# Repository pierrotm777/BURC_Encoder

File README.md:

# BURC_Encoder
 Universal RC Box System.  
 
 The BURC modules use the RCUL protocol by Rc-Navy.

## Rc-Navy
The BURC system is build by Philippe Loussouarn ([Rc-Navy](http://p.loussouarn.free.fr/index.html)). 

## Presentation of the BURC system
[What's BURC](https://p-loussouarn-free-fr.translate.goog/arduino/exemple/RCUL/RCUL.html?_x_tr_sch=http&_x_tr_sl=auto&_x_tr_tl=en&_x_tr_hl=en)

## Compatibles modules usable with BURC
All these modules behind
- [Ms8 v2](https://github.com/Ingwie/OpenAVRc_Hw/tree/V3/MutltiSwitch_Sw8_V2)  
- [Ms16](https://github.com/Ingwie/OpenAVRc_Hw/tree/V3/MultiSwitch_Sw16-ProMicro)  
- [Sound&SmokeModule](https://github.com/Ingwie/OpenAVRc_Hw/tree/V3/Sound%26SmokeModule)  
- [Xany2Msx](https://github.com/Ingwie/OpenAVRc_Hw/tree/V3/Xany2Msx/Firmware_Msx)  
- [Xany2Misc](https://github.com/Ingwie/OpenAVRc_Hw/tree/V3/Xany2Msx/Firmware_Misc)  
- Hall sensor:  
  * [Hall I2C sensor](https://github.com/Ingwie/OpenAVRc_Hw/tree/V3/Capteur_Hall_I2C)  
  * [Hall I2C sensor mini](https://github.com/Ingwie/OpenAVRc_Hw/tree/V3/Capteur_Hall_I2C_Mini)  
- [MultiSwitch_MosFet](https://github.com/Ingwie/OpenAVRc_Hw/tree/V3/MultiSwitch_MosFet)  
- [Ms8 Pulseq](https://github.com/Ingwie/OpenAVRc_Hw/tree/V3/PulseSeq) 
- [Servo 360°]() 

## Build BURC
### Schematic  
Encoder:  
  
16 switchs by I2C bus:  
  
16 switchs on Arduino:  

### Boards  
Two cards make up the BURC system.
The BURC Encoder is connected to the transmitter over a **CPPM** input or a **SBUS** input.
- The BURC Encoder:
  * Encoder board (include 8 switchs, 1 360° hall sensor and 1 slider, need one proportional channel) 
  Can command up to 128 fonctions (8x16) by exemple 8 Ms16 modules, use 1 channel for each 16 switchs module.  

  <table border="2">
  <tr>
  <td></td>
  <td></td>
  </tr>
  </table>
  
  The hall sensor command a Schottel motor type by rotation, and the slider command the motor's power.  
  This board is the **main board** system and can command **several 16 switchs** board.  
  The interface between all the boards use an **I2C** bus.  

  The same board can be used for the left or right motor, and assume to wire only one of the two hall sensor an the 8 first switchs.  
  The second board will command the 8 other switchs and the second slider (No need another arduino Pro Mini in the second circuit board) .  
  An Attiny85 receive these orders from the first board and command the second hall sensor and the second slider.  
  A dashboard exemple for two motors:  
  <table border="2">
  <tr>
  <td></td>
  </tr>
  </table>
    
  * Encoder symplified board (include 16 switchs or 8 switchs and 6 potentiometers, need one proportional channel) 
  Can command up to 128 fonctions (8x16) by exemple 8 Ms16 modules, use 1 channel for each 16 switchs module.  

  <table border="2">
  <tr>
  <td></td>
  </tr>
  </table>
  
  You need to remove the resistor's LED on pin D13 (C10 signal).  

- The Switch board:

  16 Switchs board (need one proportional channel) 
  Each switch can command 1 fonction.  
  The type of command depend of the [Ms8](https://github.com/Ingwie/OpenAVRc_Hw/blob/V3/MutltiSwitch_Sw8_V2/MS8-Xany-V2_Manuel_Utilisateur.pdf)/[Ms16](https://github.com/Ingwie/OpenAVRc_Hw/blob/V3/MultiSwitch_Sw16-ProMicro/MS16-Xany_Manuel_Utilisateur.pdf) possibilities.    
  This board read 16 switchs by 1 MCP23017 or 2 PCF8574 or 1 PCF8575.
  <table border="2">
  <tr>
  <td></td>
  <td></td>
  </tr>
  </table>  
  
  A main board coupled to  a second board and 2 16 switchs boards:
  <table border="2">
  <tr>
  <td></td>
  </tr>
  </table>  
  
  A main board and a 48 switchs coupled:
  <table border="2">
  <tr>
  <td></td>
  </tr>
  </table>  

### Firmware upload for Pro Mini
- Windows:  
The best method is to use [Xloader](https://github.com/pierrotm777/BURC_Encoder/blob/main/PROG/Windows/XLoader.zip).  
The last firmware is the version [v0.14](https://github.com/pierrotm777/BURC_Encoder/blob/main/PROG/Windows/BURC_CODER_V0_14.hex).  

- Other Os:
Use you Arduino IDE for find witch command to use.
In my case, the command is :  
  
  * replace the hex file path C:\Users\pierrot\AppData\Local\Temp\arduino_build_879913/Blink.ino.hex by your firmware path.  
  * create a script file with this change.  

### Firmware upload for Attiny85
  * use an USBAsp programmer and [ARDUDESS Gui](https://github.com/ZakKemble/AVRDUDESS/releases/) or an [Arduino Uno board](https://www.instructables.com/Programming-ATtinys-Micro-Controllers-With-Arduino)
  * define the fuses (for 16Mhz internal mode), low=0xF1, high=0xDF, extended=0xFF
  * last firmware is the version [v2.2](https://github.com/pierrotm777/BURC_Encoder/blob/main/PROG/Windows/HallAna2A1335_V2_2.hex).  

### Exemple BURC build
- You will find [here](https://cults3d.com/fr/mod%C3%A8le-3d/jeu/burc-pad) an exemple of 3d files by **croky_b** witch accept all the BURC's boards.  

## Configure the BURC Encoder
  * Pro Mini:
    * Connect a FTDI interface to the Arduino Pro Mini and your PC.
    * Use a terminal for send your commands.
    * Set your terminal with 115200 bauds, 8 bits, no parity, 1 bit stop and CR or CRLF (see LIGNE.TERM).
    * Type ENTER key for see the module's version.

  * Attiny85 (360° encoder) A push button allows:
    * calibrating the analog sensor (min and max): before powering the ATtiny85, press the Push button and hold it for  1 - 2 seconds.
    * setting the I2C address: before powering the ATtiny85, press the Push button and hold it for more than 4 seconds.  
      Additionally, it can read an analogic input (0/5V)

## Settings usables
The list of messages that can be transported in each RCUL instance is:  
- SW1-SW8:   the state of 8 contacts of the 8 contacts of an 8 I/O I/O extender or a 16 I/O extender or the first 8 contacts of the 16 native contacts of the Arduino
- SW9-SW16:  the state of the last 8 contacts of a 16 I/O extender or the last 8 contacts of the 16 native contacts of the Arduino
- SW1-SW16:  the state of 16 contacts of a 16 I/O extender or of the 16 native contacts of the Arduino
- ANGLE:     the value of the angle of a 360° angle sensor
- ANGLE+ANA: the value of the angle of a 360° angular sensor + an analog value  

On the encoder there are 16 native contacts from C1 to C16.  
Among C8 to C16, 6 are also analog inputs which correspond to pins C11 to C16.  
So C11 to C16 are also ANA1 to ANA6 (these are my names, not the names of the "arduino" pins):  
We therefore have 6 analog channels at our disposal (just as we wire a pot there instead of an switch or push button).  

We can make extended RCUL messages of the type:  
**RCUL1.MESSAGE=C1-C8@0x00+ANA1** (which will transmit 8 contact states + an 8-bit ana value:  
You obviously have to wire a knob to pin C11).  
**RCUL2.MESSAGE=C9-C16@0x24+ANA2** (which will transmit 16 contact states + an 8-bit ana value:  
You obviously have to wire a knob to pin C12).  

So, with **RCUL1.MESSAGE=C1-C8@0x00+ANA1** or **RCUL2.MESSAGE=C9-C16@0x24+ANA2**,  
for an MS8 (V1 or V2), you can control the 8 outputs + the additional proportional output.  
You can also order the Sound&Smoke module which uses the 8 contacts to launch 8  
different sounds and the ana value to adjust the volume of the DF Player from the transmitter.  

We can also do:
**RCUL3.MESSAGE=C1-C16@0x25+ANA3** (which will transmit 16 contact states + an 8-bit analog value:  
You obviously have to wire a knob to pin C12)
So, with **RCUL3.MESSAGE=C1-C16@0x25+ANA3** for an MS16, you can control the 16 outputs + the additional proportional output.  

So, if we want to use the first 8 contacts C1 to C8 of your 16-input I2C extender at address 0x24,  
we just have to create another RCUL instance in which we refer to the first 8 contacts: **RCUL5.MESSAGE=C1-C8@0x24**
And with RCUL5 we can, for example, order another MS8.
So we will have the first 8 contacts of the I2C extender with 16 inputs (at address 0x24) used by RCUL5 to control an MS8 (for example) 
and the last 8 contacts of the 16-input I2C extender (at address 0x24) used by RCUL2 (which also uses ANA2) to control a Sound&Smoke.

It is possible to directly map an analog value (ANA1 to AN6), inverted or not, to a channel.  
To do this, you must use the command **RCULx.MESSAGE=RC.ANA[_INV]y** with x=RCUL instance number and y is the ANA channel number (from 1 to 6):  
Example: **RCUL4.MESSAGE=RC.ANA_INV1**  
A simple solution for build a little 6 channels hanset WITH BURC features.  

Debug method:  
To test an RCUL channel in CPPM, we loop pin8 back to pin9 and we do an **RX.MODE=RCUL4@CPPM4** and after an **RX.DBG=1** command.  

## I2C Devices address
<pre>
PCF8574         <b>0x20 to 0x23</b>  
MCP23017        <b>0x24 to 0x27</b>  
PCF8574A        <b>0x38 to 0x3B</b> (very difficult to find)  
PCF8575         <b>0x24 to 0x27</b>  
PCF8575A        <b>0x3C to 0x3F</b> (very difficult to find)  
ANGLE SENSOR    <b>0x0C to 0x0F</b>  
</pre>

Exemple of configuration:
```
CONF?
LANG=FR
LIGNE.TERM=CRLF
ECOLAGE.MODE=CPPM_OUT
CPPM.MODU=NEG
CPPM.ENTETE=300
CPPM.VOIE.NB=8
CPPM.PERIODE=22500
RCUL.REPET=2
RCUL1.VOIE=5
RCUL1.MESSAGE=ANGLE+ANA@0x0C
RCUL1.TEST=OFF
RCUL2.VOIE=6
RCUL2.MESSAGE=C9-C16@0x24
RCUL2.TEST=OFF
RCUL3.VOIE=8
RCUL3.MESSAGE=C1-C8@0x24+ANA1
RCUL3.TEST=OFF
RCUL4.VOIE=7
RCUL4.MESSAGE=RC.ANA_INV1
RCUL4.TEST=OFF
RCUL5.VOIE=OFF
RCUL5.MESSAGE=C1-C8@0x00
RCUL5.TEST=OFF
RCUL6.VOIE=OFF
RCUL6.MESSAGE=C1-C8@0x00
RCUL6.TEST=OFF
RX.MODE=RCUL6@CPPM6
RX.DBG=0
```

<pre>
- LANG=FR                       define language (FR or UK)  
- LIGNE.TERM=CRLF               define terminal return (CR or CRLF)  
- ECOLAGE.MODE=CPPM_OUT         CPPM_OUT+CPPM_IN/CPPM_OUT/SBUS_OUT;FUTABA[_INV] Defines the transmitter training mode
- CPPM.MODU=NEG                 CPPM signal is build with negative pulses (POS is possible)  
- CPPM.ENTETE=300               300 first width CPPM pulse  
- CPPM.VOIE.NB=8                CPPM build 8 channels  
- CPPM.PERIODE=22500            CPPM periode in mS
- SBUS.SPEED=NORMAL				NORMAL/FAST Defines the SBUS speed (NORMAL=14ms, FAST=7ms)  
- RCUL.REPET=2                  the encoder repeats the same thing twice for a better transmission result  
- RCUL1.MESSAGE=ANGLE+ANA@0x0C  for command an azimutal motor (direction and motor)  
- RCUL2.MESSAGE=C9-C16@0x24     8 buttons on MCP23017 (address 0x24)  
- RCUL3.MESSAGE=C1-C8@0x24+ANA1 8 buttons on MCP23017 and analog button (module Sound&Smoke for 8 sounds et volume)
- RCUL4.MESSAGE=RC.ANA_INV2     1 analogique channel inverted  
</pre>

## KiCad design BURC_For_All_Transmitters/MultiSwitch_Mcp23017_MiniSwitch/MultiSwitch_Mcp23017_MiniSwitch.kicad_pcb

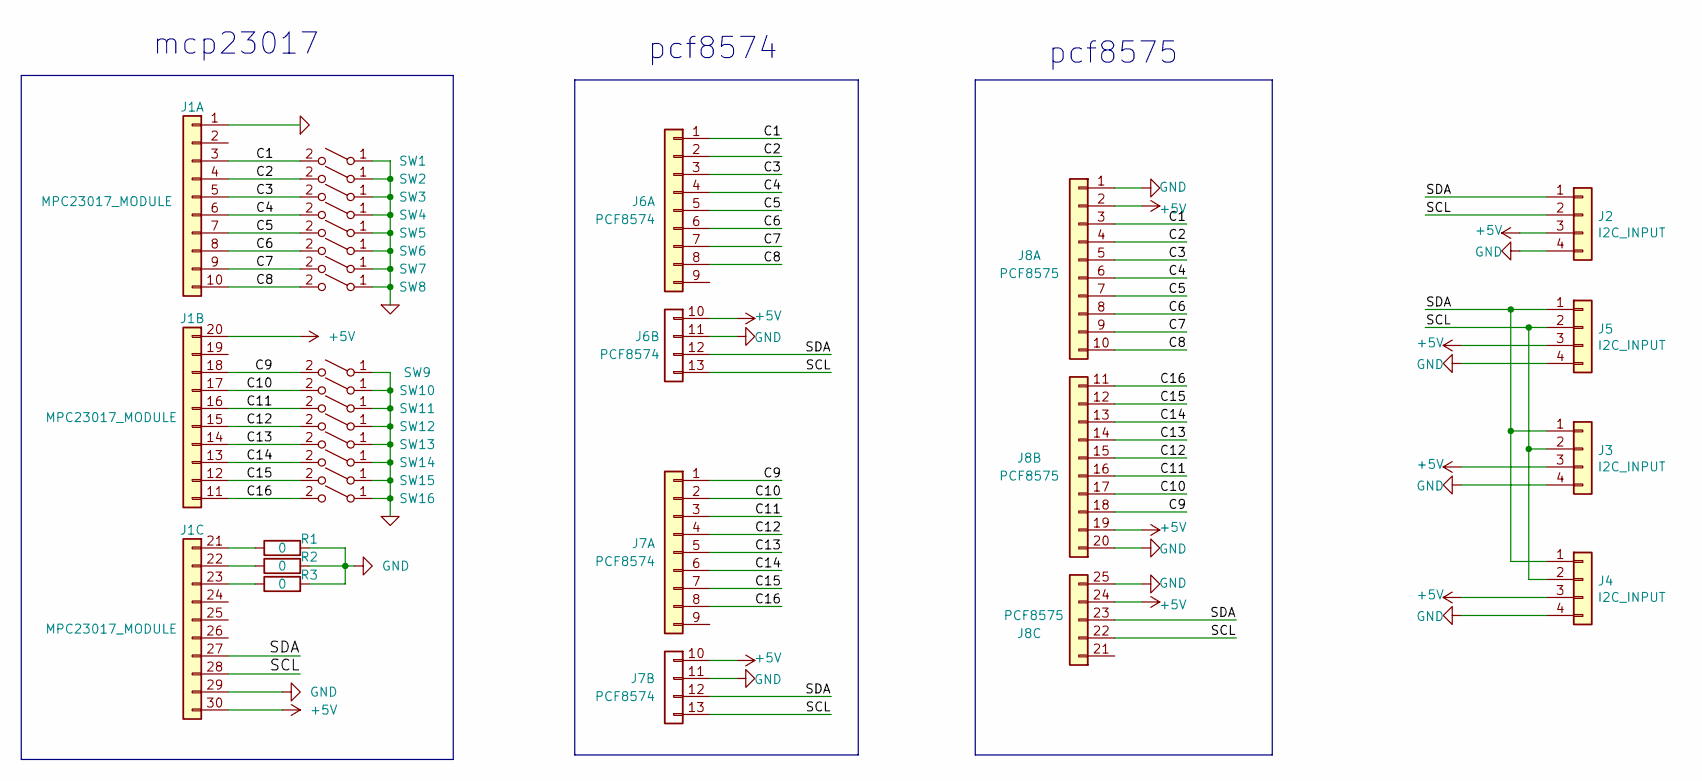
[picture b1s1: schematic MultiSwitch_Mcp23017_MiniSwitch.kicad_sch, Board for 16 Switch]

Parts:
J1: MPC23017_MODULE; MCP23017_MODULE
J2, J4: I2C_INPUT; PinHeader_1x04_P2.54mm_Horizontal
J3, J5: I2C_INPUT; PinSocket_1x04_P2.54mm_Horizontal
J6, J7: PCF8574; PCF8574_BreakOut
J8: PCF8575; PCF8575_Breakout_Dbl
R1, R2, R3: 0; R_0805_2012Metric_Pad1.20x1.40mm_HandSolder
SW1, SW2, SW3, SW4, SW5, SW6, SW7, SW8, SW9, SW10, SW11, SW12, SW13, SW14, SW15, SW16: SW_SPST; Interrupteur_SPDT_2Pins

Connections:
+5V: J1.20, J1.30, J2.3, J3.3, J4.3, J5.3, J6.10 (Pin_4), J7.10 (Pin_4), J8.2, J8.19, J8.24
/C1: J1.3, J6.1, J8.3, SW1.2 (B)
/C2: J1.4, J6.2, J8.4, SW2.2 (B)
/C3: J1.5, J6.3, J8.5, SW3.2 (B)
/C4: J1.6, J6.4, J8.6, SW4.2 (B)
/C5: J1.7, J6.5, J8.7, SW5.2 (B)
/C6: J1.8, J6.6, J8.8, SW6.2 (B)
/C7: J1.9, J6.7, J8.9, SW7.2 (B)
/C8: J1.10, J6.8, J8.10, SW8.2 (B)
/C9: J1.18, J7.1, J8.18, SW9.2 (B)
/C10: J1.17, J7.2, J8.17, SW10.2 (B)
/C11: J1.16, J7.3, J8.16, SW11.2 (B)
/C12: J1.15, J7.4, J8.15, SW12.2 (B)
/C13: J1.14, J7.5, J8.14, SW13.2 (B)
/C14: J1.13, J7.6, J8.13, SW14.2 (B)
/C15: J1.12, J7.7, J8.12, SW15.2 (B)
/C16: J1.11, J7.8, J8.11, SW16.2 (B)
/SCL: J1.28, J2.2, J3.2, J4.2, J5.2, J6.13 (Pin_1), J7.13 (Pin_1), J8.22
/SDA: J1.27, J2.1, J3.1, J4.1, J5.1, J6.12 (Pin_2), J7.12 (Pin_2), J8.23
GND: J1.1, J1.29, J2.4, J3.4, J4.4, J5.4, J6.11 (Pin_3), J7.11 (Pin_3), J8.1, J8.20, J8.25, R1.2, R2.2, R3.2, SW1.1 (A), SW2.1 (A), SW3.1 (A), SW4.1 (A), SW5.1 (A), SW6.1 (A), SW7.1 (A), SW8.1 (A), SW9.1 (A), SW10.1 (A), SW11.1 (A), SW12.1 (A), SW13.1 (A), SW14.1 (A), SW15.1 (A), SW16.1 (A)
unnamed: J1.21, R1.1
unnamed: J1.22, R2.1
unnamed: J1.23, R3.1

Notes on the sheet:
pcf8575
pcf8574
mcp23017

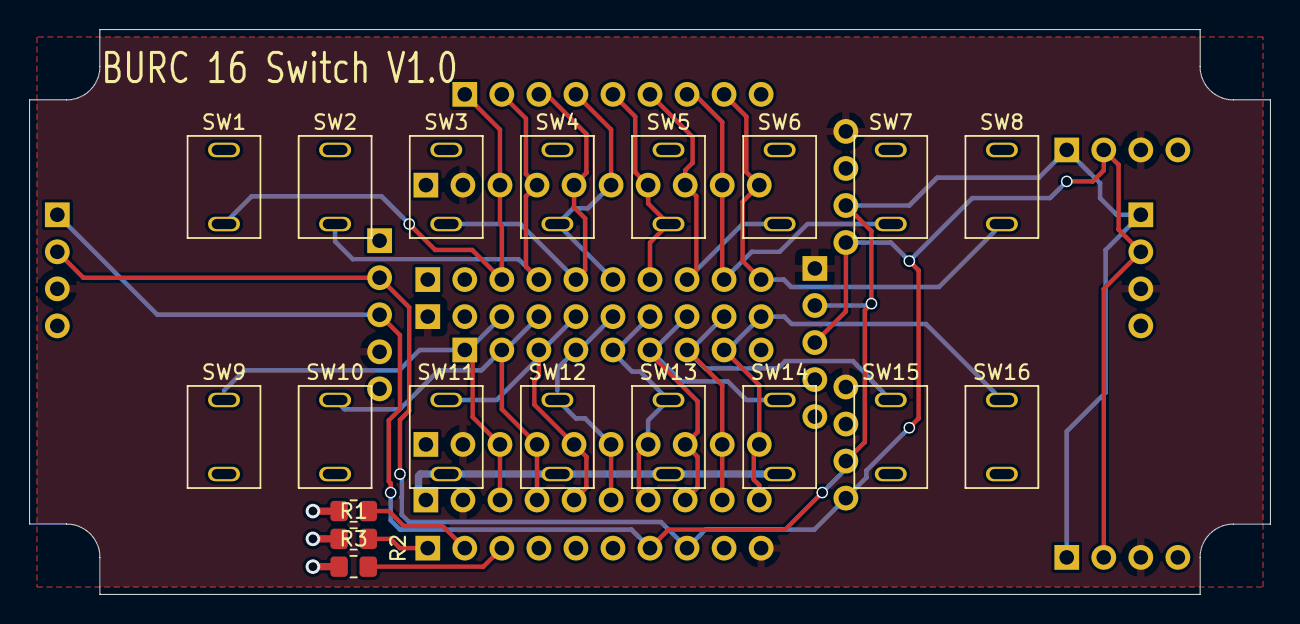
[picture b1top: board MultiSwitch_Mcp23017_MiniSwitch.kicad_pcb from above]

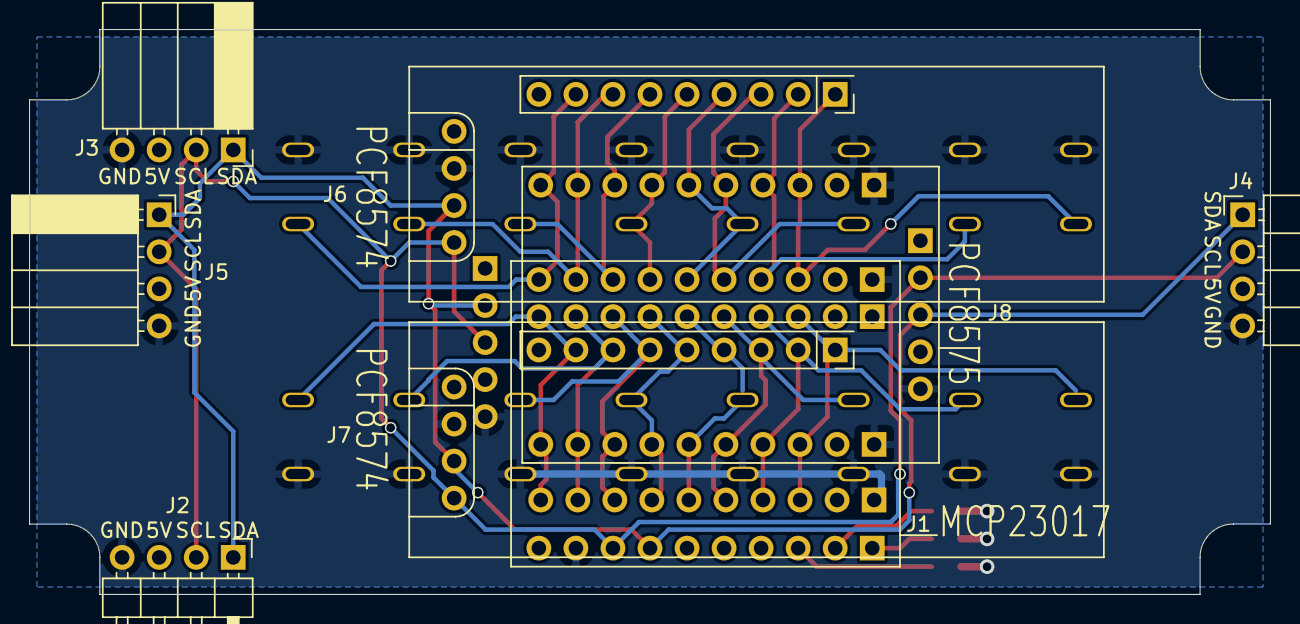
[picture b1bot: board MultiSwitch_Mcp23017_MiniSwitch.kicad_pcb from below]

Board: 2 copper layers, 85.1 x 38.7 mm, 27 parts (8 on the bottom side), 23 nets.

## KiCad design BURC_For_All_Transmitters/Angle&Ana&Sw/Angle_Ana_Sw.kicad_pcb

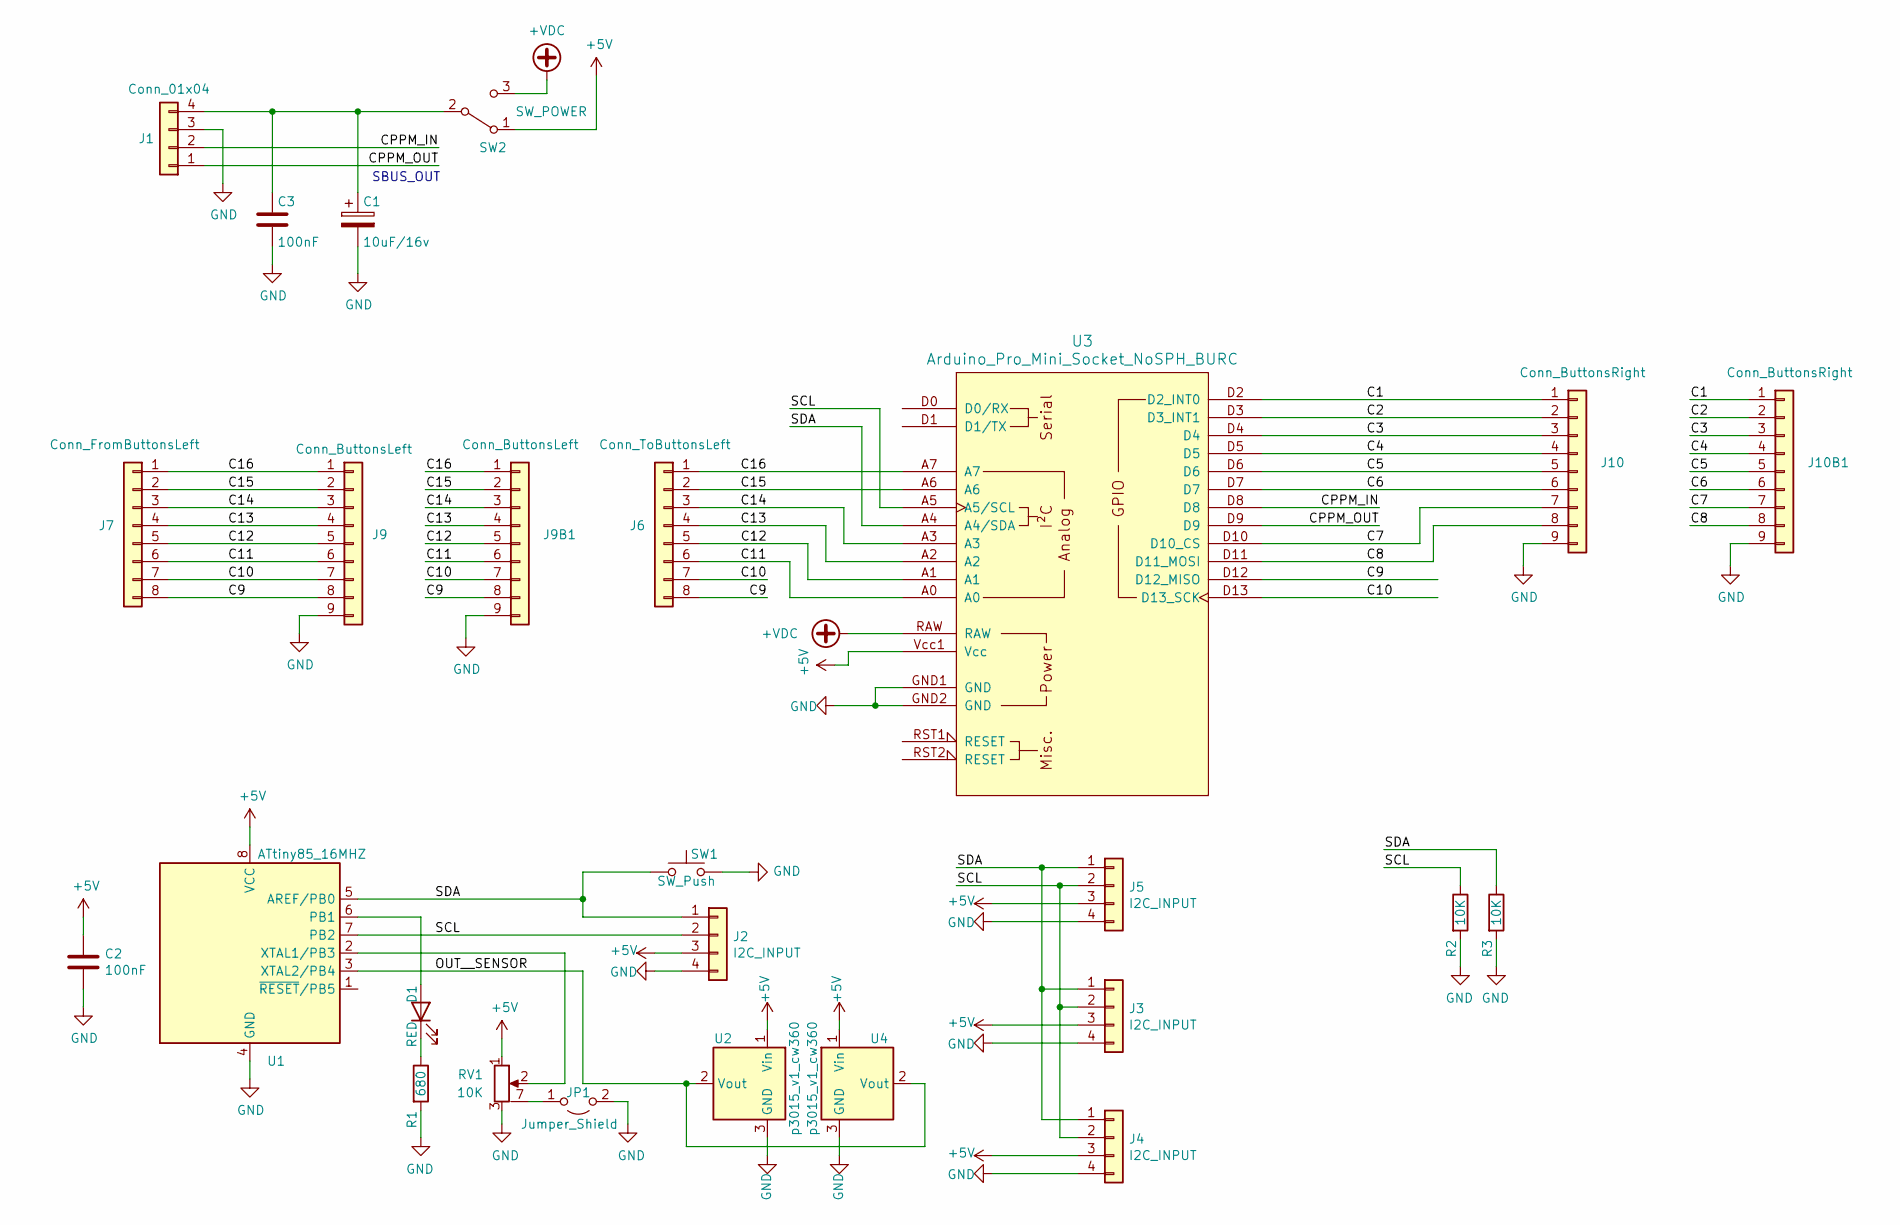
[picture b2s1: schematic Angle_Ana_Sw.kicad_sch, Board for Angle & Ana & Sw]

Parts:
C1: 10uF/16v; C_Radial_D8.0mm_H7.0mm_P3.50mm
C2, C3: 100nF; C_Rect_L7.0mm_W3.5mm_P5.00mm
D1: RED; LED_D3.0mm_Horizontal_O1.27mm_Z2.0mm
J1: Conn_01x04; PinHeader_1x04_P2.54mm_Horizontal
J2, J4: I2C_INPUT; PinHeader_1x04_P2.54mm_Horizontal
J3, J5: I2C_INPUT; PinSocket_1x04_P2.54mm_Horizontal
J6: Conn_ToButtonsLeft; PinSocket_2x04_P2.54mm_Horizontal
J7: Conn_FromButtonsLeft; PinHeader_2x04_P2.54mm_Horizontal
J9: Conn_ButtonsLeft; JST_PH_B9B-PH-K_1x09_P2.00mm_Vertical
J9B1: Conn_ButtonsLeft; PinHeader_1x09_P2.54mm_Vertical
J10: Conn_ButtonsRight; JST_PH_B9B-PH-K_1x09_P2.00mm_Vertical
J10B1: Conn_ButtonsRight; PinHeader_1x09_P2.54mm_Vertical
JP1: Jumper_Shield; SolderJumper-2_P1.3mm_Open_Pad1.0x1.5mm
R1: 680; R_Axial_DIN0204_L3.6mm_D1.6mm_P5.08mm_Horizontal
R2, R3: 10K; R_Axial_DIN0204_L3.6mm_D1.6mm_P5.08mm_Horizontal
RV1: 10K; PTA2043-2015CPB103
SW1: SW_Push; SW_PUSH_ANGLED
SW2: SW_POWER; PinHeader_1x03_P2.54mm_Vertical
U1: ATtiny85_16MHZ; DIP-8_W7.62mm
U2, U4: p3015_v1_cw360
U3: Arduino_Pro_Mini_Socket_NoSPH_BURC

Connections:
+5V: C2.1, J2.3, J3.3, J4.3, J5.3, RV1.1, SW2.1 (A), U1.8 (VCC), U2.1 (Vin), U3.Vcc1 (Vcc), U4.1 (Vin)
+VDC: SW2.3 (C), U3.RAW
/C1: J10.1, J10B1.1, U3.D2 (D2_INT0)
/C2: J10.2, J10B1.2, U3.D3 (D3_INT1)
/C3: J10.3, J10B1.3, U3.D4
/C4: J10.4, J10B1.4, U3.D5
/C5: J10.5, J10B1.5, U3.D6
/C6: J10.6, J10B1.6, U3.D7
/C7: J10.7, J10B1.7, U3.D10 (D10_CS)
/C8: J10.8, J10B1.8, U3.D11 (D11_MOSI)
/C9: J6.8, J7.8, J9.8, J9B1.8, U3.D12 (D12_MISO)
/C10: J6.7, J7.7, J9.7, J9B1.7, U3.D13 (D13_SCK)
/C11: J6.6, J7.6, J9.6, J9B1.6, U3.A0
/C12: J6.5, J7.5, J9.5, J9B1.5, U3.A1
/C13: J6.4, J7.4, J9.4, J9B1.4, U3.A2
/C14: J6.3, J7.3, J9.3, J9B1.3, U3.A3
/C15: J6.2, J7.2, J9.2, J9B1.2, U3.A6
/C16: J6.1, J7.1, J9.1, J9B1.1, U3.A7
/CPPM_IN: J1.2, U3.D8
/CPPM_OUT: J1.1, U3.D9
/OUT__SENSOR: U1.3 (XTAL2/PB4), U2.2 (Vout), U4.2 (Vout)
/SCL: J2.2, J3.2, J4.2, J5.2, R2.1, U1.7 (PB2), U3.A5 (A5/SCL)
/SDA: J2.1, J3.1, J4.1, J5.1, R3.1, SW1.1, U1.5 (AREF/PB0), U3.A4 (A4/SDA)
GND: C1.2, C2.2, C3.2, J1.3, J2.4, J3.4, J4.4, J5.4, J9.9, J9B1.9, J10.9, J10B1.9, JP1.2 (B), R1.2, R2.2, R3.2, RV1.3, SW1.2, U1.4 (GND), U2.3 (GND), U3.GND1 (GND), U3.GND2 (GND), U4.3 (GND)
unnamed: D1.2 (A), U1.6 (PB1)
unnamed: D1.1 (K), R1.1
unnamed: C1.1, C3.1, J1.4, SW2.2 (B)
unnamed: JP1.1 (A), RV1.7 (Shield)
unnamed: RV1.2, U1.2 (XTAL1/PB3)

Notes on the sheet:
SBUS_OUT

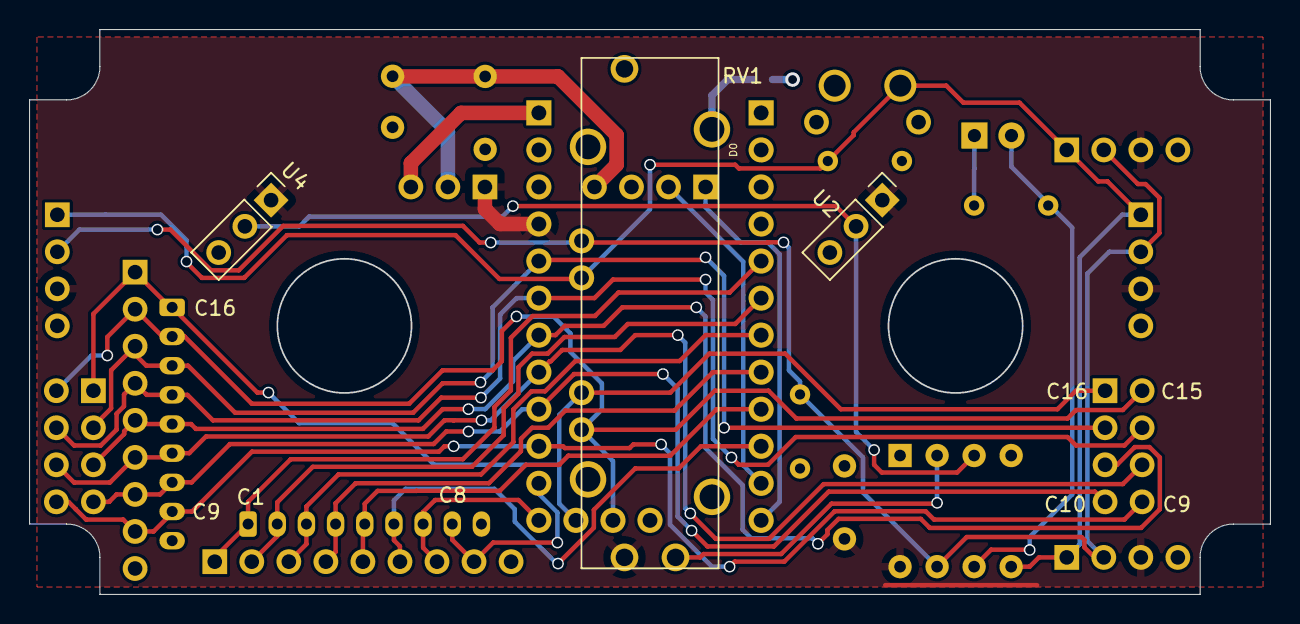
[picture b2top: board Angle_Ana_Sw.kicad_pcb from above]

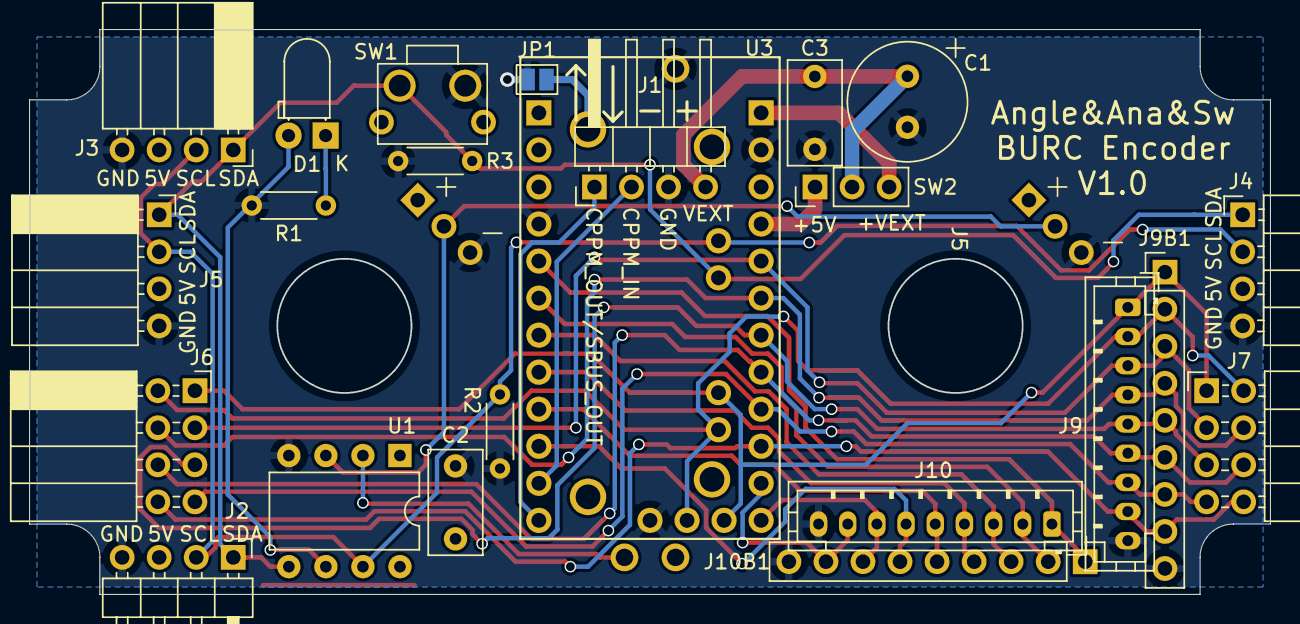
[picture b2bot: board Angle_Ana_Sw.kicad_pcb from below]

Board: 2 copper layers, 85.0 x 38.7 mm, 26 parts (23 on the bottom side), 29 nets.

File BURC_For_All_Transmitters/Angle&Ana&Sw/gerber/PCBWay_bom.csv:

designator,quantity,value,pack,mpn,mount_type
C1,1,10uF/16v,C_Radial_D8.0mm_H7.0mm_P3.50mm,,tht
"C2, C3",2,100nF,C_Rect_L7.0mm_W3.5mm_P5.00mm,,tht
D1,1,RED,LED_D3.0mm_Horizontal_O1.27mm_Z2.0mm,,tht
J1,1,Conn_01x04,PinHeader_1x04_P2.54mm_Horizontal,,tht
"J10, J9",2,Conn_ButtonsLeft,JST_PH_B9B-PH-K_1x09_P2.00mm_Vertical,,tht
"J2, J4",2,I2C_INPUT,PinHeader_1x04_P2.54mm_Horizontal,,tht
"J3, J5",2,I2C_INPUT,PinSocket_1x04_P2.54mm_Horizontal,,tht
J6,1,Conn_ToButtonsRight,PinSocket_2x04_P2.54mm_Horizontal,,tht
J7,1,Conn_FromButtonsLeft,PinHeader_2x04_P2.54mm_Horizontal,,tht
R1,1,680,R_Axial_DIN0204_L3.6mm_D1.6mm_P5.08mm_Horizontal,,tht
RV1,1,10K,PTA2043-2015CPB103,,tht
SW1,1,SW_Push,SW_PUSH_ANGLED,,tht
SW2,1,SW_POWER,PinHeader_1x03_P2.54mm_Vertical,,tht
U1,1,ATtiny85,DIP-8_W7.62mm,,tht
"U2, U4",2,p3015_v1_cw360,p3015_v1_cw360,,tht
U3,1,Arduino_Pro_Mini,Arduino_Pro_Mini_Socket_NoSPH_BURC,,tht

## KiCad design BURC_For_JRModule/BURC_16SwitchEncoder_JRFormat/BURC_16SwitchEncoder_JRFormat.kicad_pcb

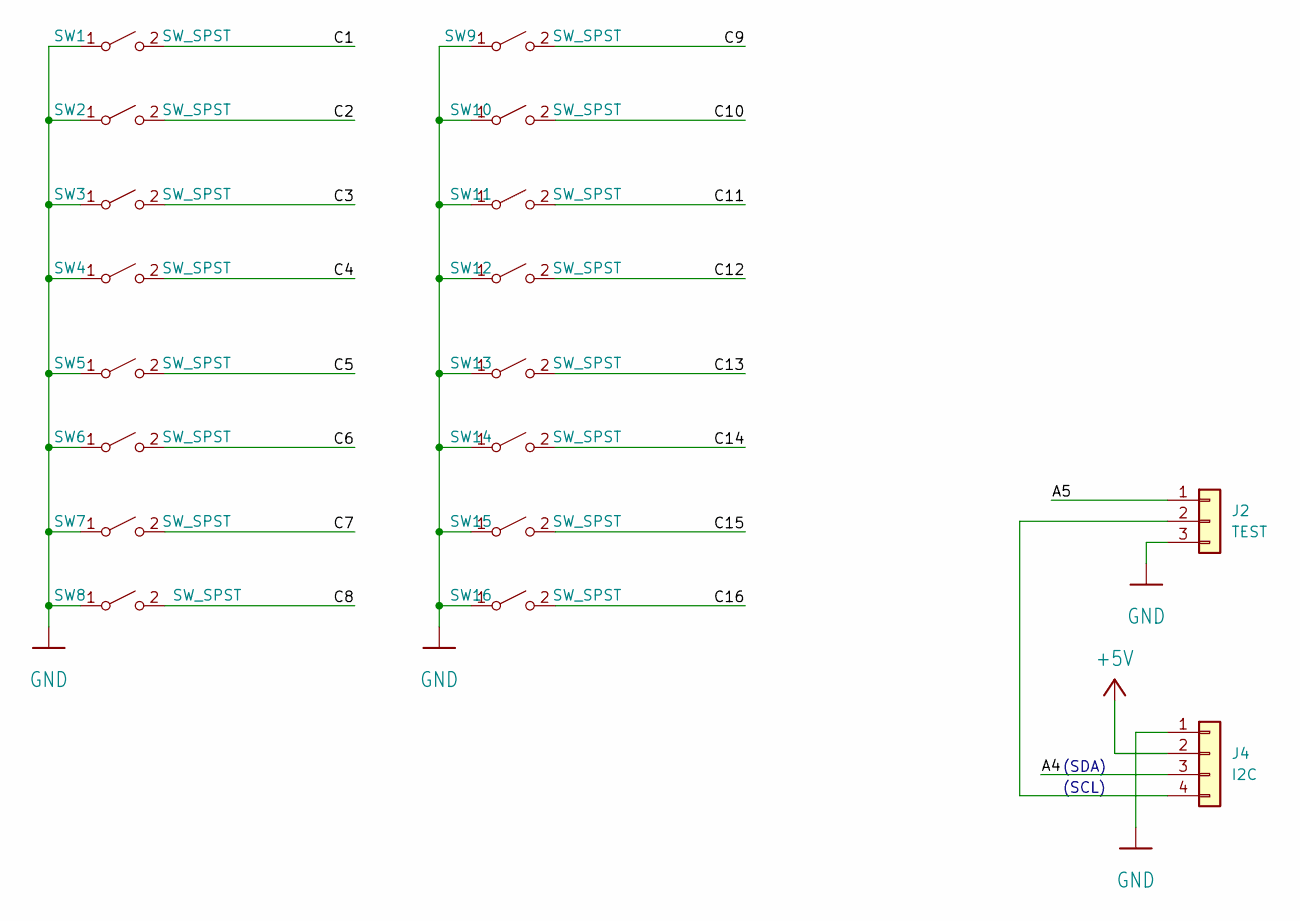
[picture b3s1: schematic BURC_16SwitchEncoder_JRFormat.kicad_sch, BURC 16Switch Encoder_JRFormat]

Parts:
J2: TEST; PinSocket_1x03_P2.54mm_Vertical
J4: I2C; PinHeader_1x04_P2.54mm_Vertical
SW1, SW2, SW3, SW4, SW5, SW6, SW7, SW8, SW9, SW10, SW11, SW12, SW13, SW14, SW15, SW16: SW_SPST; Interrupteur_SPDT_2Pins

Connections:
+5V: J4.2
/A4: J4.3
/A5: J2.1
/C1: SW1.2 (B)
/C2: SW2.2 (B)
/C3: SW3.2 (B)
/C4: SW4.2 (B)
/C5: SW5.2 (B)
/C6: SW6.2 (B)
/C7: SW7.2 (B)
/C8: SW8.2 (B)
/C9: SW9.2 (B)
/C10: SW10.2 (B)
/C11: SW11.2 (B)
/C12: SW12.2 (B)
/C13: SW13.2 (B)
/C14: SW14.2 (B)
/C15: SW15.2 (B)
/C16: SW16.2 (B)
GND: J2.3, J4.1, SW1.1 (A), SW2.1 (A), SW3.1 (A), SW4.1 (A), SW5.1 (A), SW6.1 (A), SW7.1 (A), SW8.1 (A), SW9.1 (A), SW10.1 (A), SW11.1 (A), SW12.1 (A), SW13.1 (A), SW14.1 (A), SW15.1 (A), SW16.1 (A)
unnamed: J2.2, J4.4

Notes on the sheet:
(SDA)
(SCL)

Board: 2 copper layers, 18 parts (0 on the bottom side), 2 nets, no tracks yet.

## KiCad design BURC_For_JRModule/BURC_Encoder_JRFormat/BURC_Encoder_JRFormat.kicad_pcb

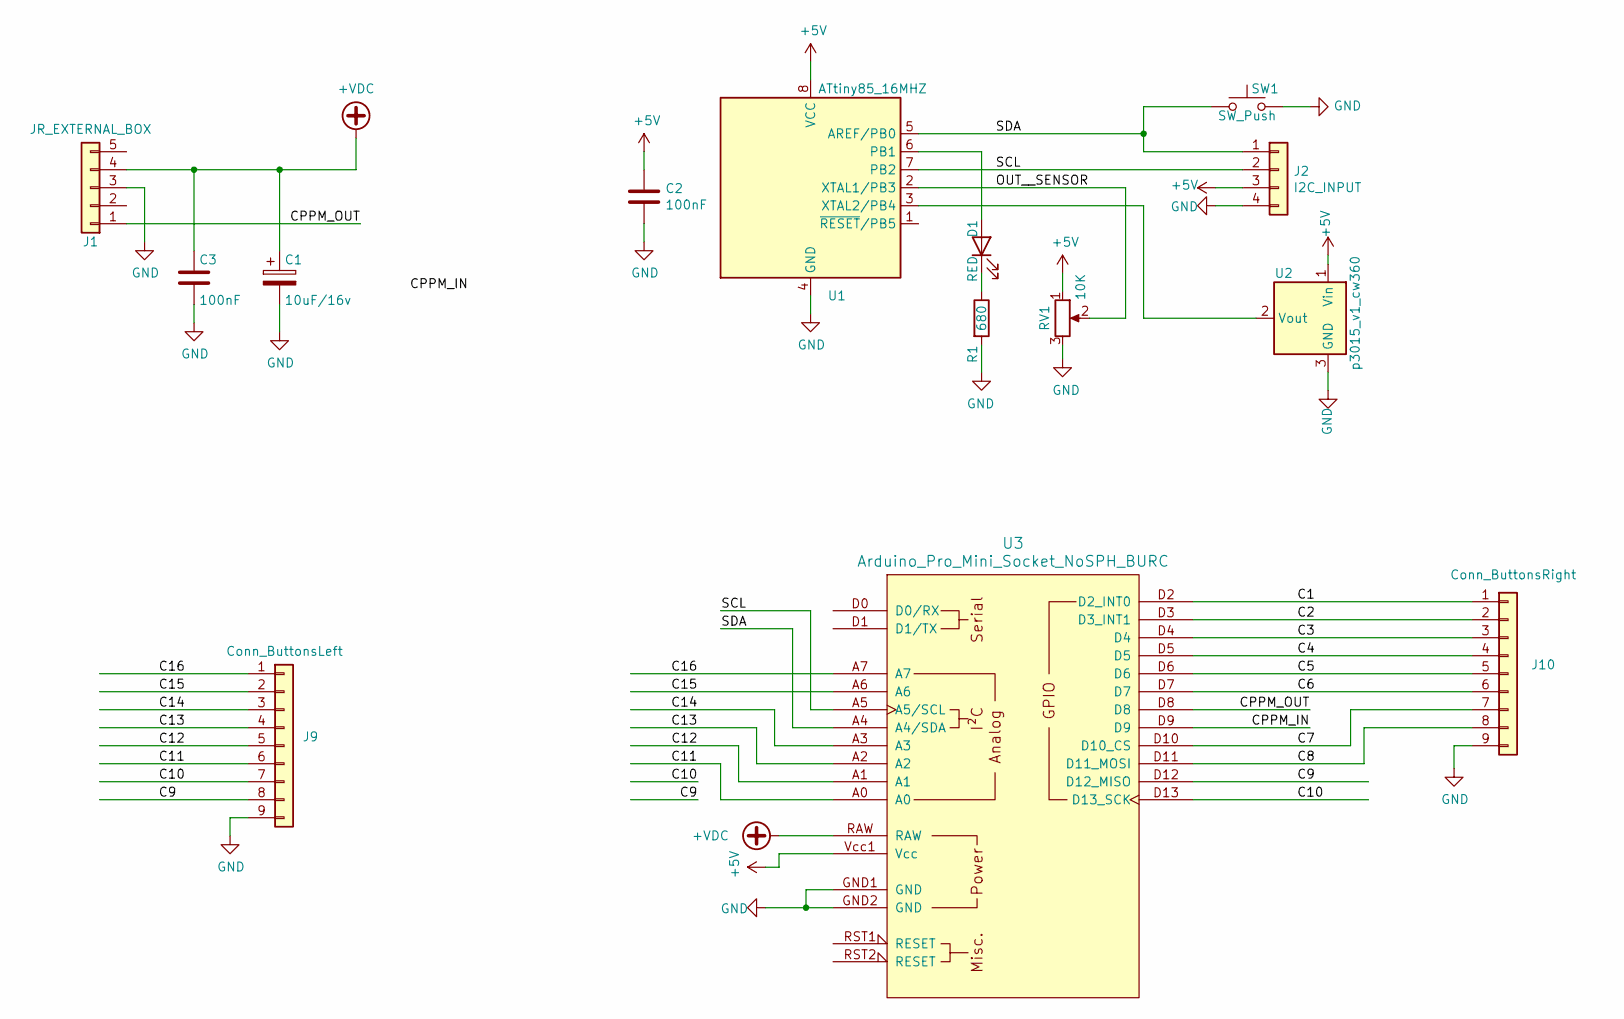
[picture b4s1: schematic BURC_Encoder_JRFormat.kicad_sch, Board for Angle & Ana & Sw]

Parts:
C1: 10uF/16v; C_Radial_D8.0mm_H7.0mm_P3.50mm
C2, C3: 100nF; C_Rect_L7.0mm_W3.5mm_P5.00mm
D1: RED; LED_D3.0mm
J1: JR_EXTERNAL_BOX; 4455-B05
J2: I2C_INPUT; PinHeader_1x04_P2.54mm_Vertical
J9: Conn_ButtonsLeft; JST_PH_B9B-PH-K_1x09_P2.00mm_Vertical
J10: Conn_ButtonsRight; JST_PH_B9B-PH-K_1x09_P2.00mm_Vertical
R1: 680; R_Axial_DIN0204_L3.6mm_D1.6mm_P5.08mm_Horizontal
RV1: 10K; PTA2043-2015CPB103
SW1: SW_Push; SW_PUSH_6mm_H4.3mm
U1: ATtiny85_16MHZ; DIP-8_W7.62mm
U2: p3015_v1_cw360
U3: Arduino_Pro_Mini_Socket_NoSPH_BURC

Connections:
+5V: C2.1, J2.3, RV1.1, U1.8 (VCC), U2.1 (Vin), U3.Vcc1 (Vcc)
+VDC: C1.1, C3.1, J1.4, U3.RAW
/C1: J10.1, U3.D2 (D2_INT0)
/C2: J10.2, U3.D3 (D3_INT1)
/C3: J10.3, U3.D4
/C4: J10.4, U3.D5
/C5: J10.5, U3.D6
/C6: J10.6, U3.D7
/C7: J10.7, U3.D10 (D10_CS)
/C8: J10.8, U3.D11 (D11_MOSI)
/C9: J9.8, U3.D12 (D12_MISO)
/C10: J9.7, U3.D13 (D13_SCK)
/C11: J9.6, U3.A0
/C12: J9.5, U3.A1
/C13: J9.4, U3.A2
/C14: J9.3, U3.A3
/C15: J9.2, U3.A6
/C16: J9.1, U3.A7
/CPPM_IN: U3.D9
/CPPM_OUT: J1.1, U3.D8
/OUT__SENSOR: RV1.2, U1.2 (XTAL1/PB3)
/SCL: J2.2, U1.7 (PB2), U3.A5 (A5/SCL)
/SDA: J2.1, SW1.1, U1.5 (AREF/PB0), U3.A4 (A4/SDA)
GND: C1.2, C2.2, C3.2, J1.3, J2.4, J9.9, J10.9, R1.2, RV1.3, SW1.2, U1.4 (GND), U2.3 (GND), U3.GND1 (GND), U3.GND2 (GND)
unnamed: D1.2 (A), U1.6 (PB1)
unnamed: D1.1 (K), R1.1
unnamed: U1.3 (XTAL2/PB4), U2.2 (Vout)

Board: 2 copper layers, 14 parts (1 on the bottom side), 26 nets, no tracks yet.

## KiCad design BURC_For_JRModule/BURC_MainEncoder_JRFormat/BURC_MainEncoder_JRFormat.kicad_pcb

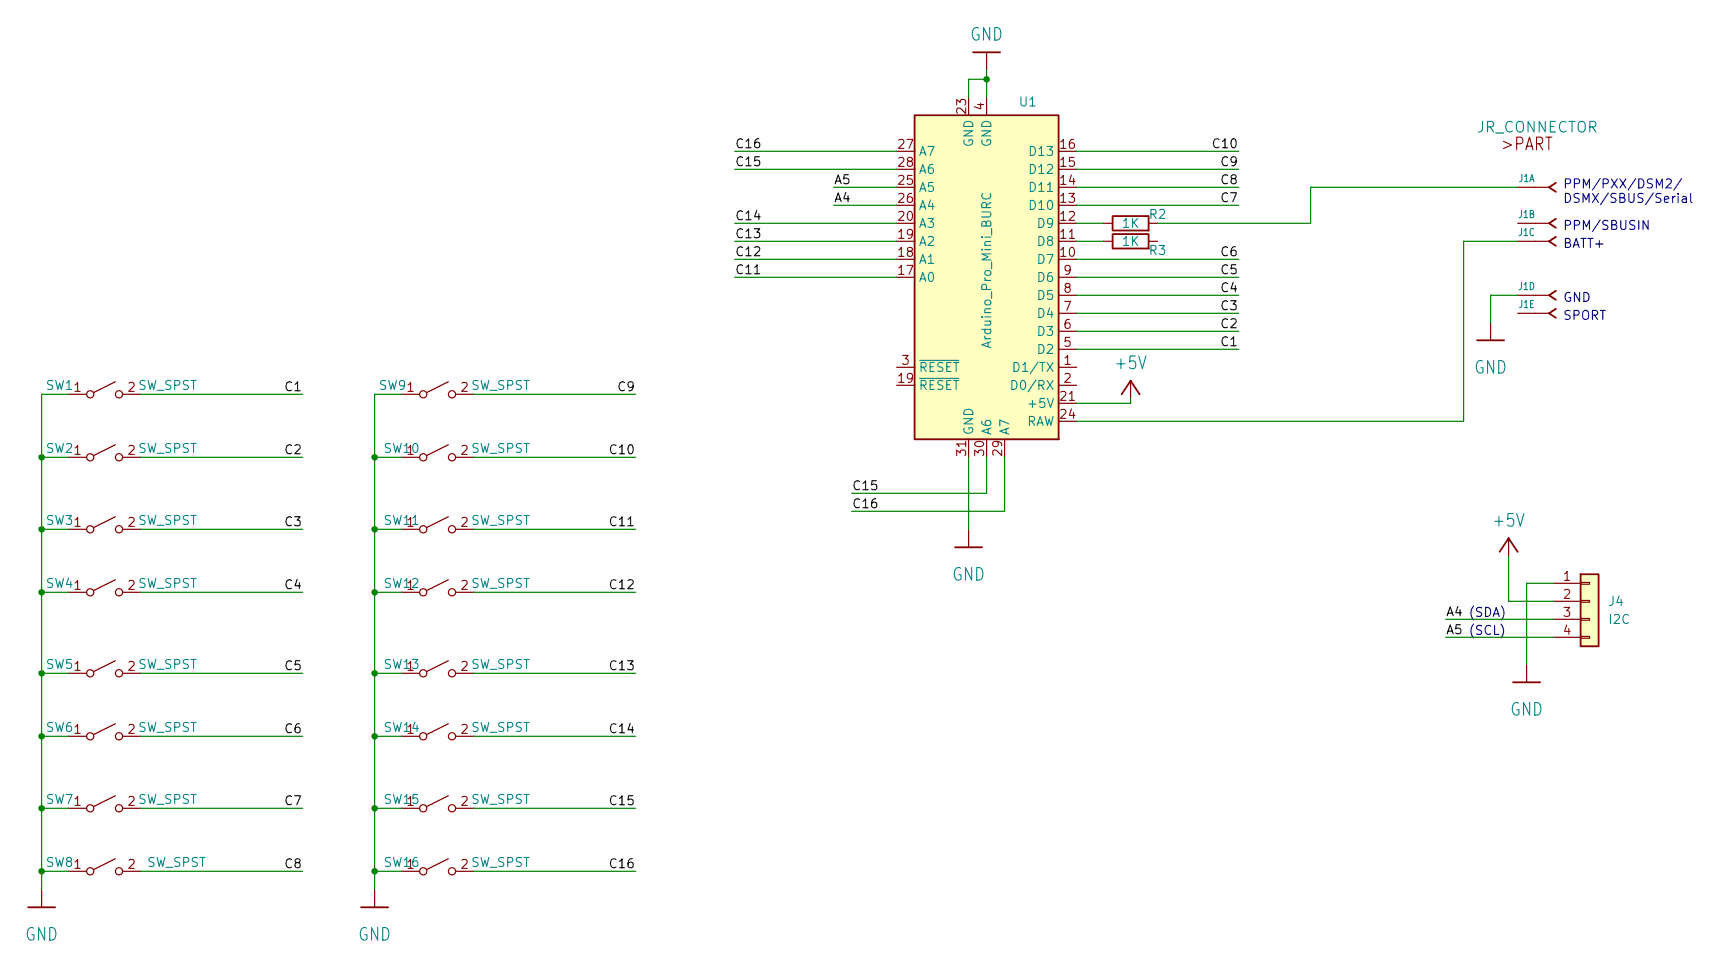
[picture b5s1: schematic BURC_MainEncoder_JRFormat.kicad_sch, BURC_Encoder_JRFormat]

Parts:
J1: JR_CONNECTOR; 4455-B05
J4: I2C; PinHeader_1x04_P2.54mm_Vertical
R2, R3: 1K; R_1206_3216Metric_Pad1.30x1.75mm_HandSolder
SW1, SW2, SW3, SW4, SW5, SW6, SW7, SW8, SW9, SW10, SW11, SW12, SW13, SW14, SW15, SW16: SW_SPST; Interrupteur_SPDT_2Pins
U1: Arduino_Pro_Mini_BURC

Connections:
+5V: J4.2, U1.21 (+5V)
/A4: J4.3, U1.26 (A4)
/A5: J4.4, U1.25 (A5)
/C1: SW1.2 (B), U1.5 (D2)
/C2: SW2.2 (B), U1.6 (D3)
/C3: SW3.2 (B), U1.7 (D4)
/C4: SW4.2 (B), U1.8 (D5)
/C5: SW5.2 (B), U1.9 (D6)
/C6: SW6.2 (B), U1.10 (D7)
/C7: SW7.2 (B), U1.13 (D10)
/C8: SW8.2 (B), U1.14 (D11)
/C9: SW9.2 (B), U1.15 (D12)
/C10: SW10.2 (B), U1.16 (D13)
/C11: SW11.2 (B), U1.17 (A0)
/C12: SW12.2 (B), U1.18 (A1)
/C13: SW13.2 (B), U1.19 (A2)
/C14: SW14.2 (B), U1.20 (A3)
/C15: SW15.2 (B), U1.28 (A6), U1.30 (A6)
/C16: SW16.2 (B), U1.27 (A7), U1.29 (A7)
GND: J1.4 (J), J4.1, SW1.1 (A), SW2.1 (A), SW3.1 (A), SW4.1 (A), SW5.1 (A), SW6.1 (A), SW7.1 (A), SW8.1 (A), SW9.1 (A), SW10.1 (A), SW11.1 (A), SW12.1 (A), SW13.1 (A), SW14.1 (A), SW15.1 (A), SW16.1 (A), U1.4 (GND), U1.23 (GND), U1.31 (GND)
unnamed: J1.1 (J), R2.2
unnamed: J1.3 (J), U1.24 (RAW)
unnamed: R3.1, U1.11 (D8)
unnamed: R2.1, U1.12 (D9)

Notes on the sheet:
SPORT
(SDA)
BATT+
GND
(SCL)
PPM/PXX/DSM2/ DSMX/SBUS/Serial
PPM/SBUSIN

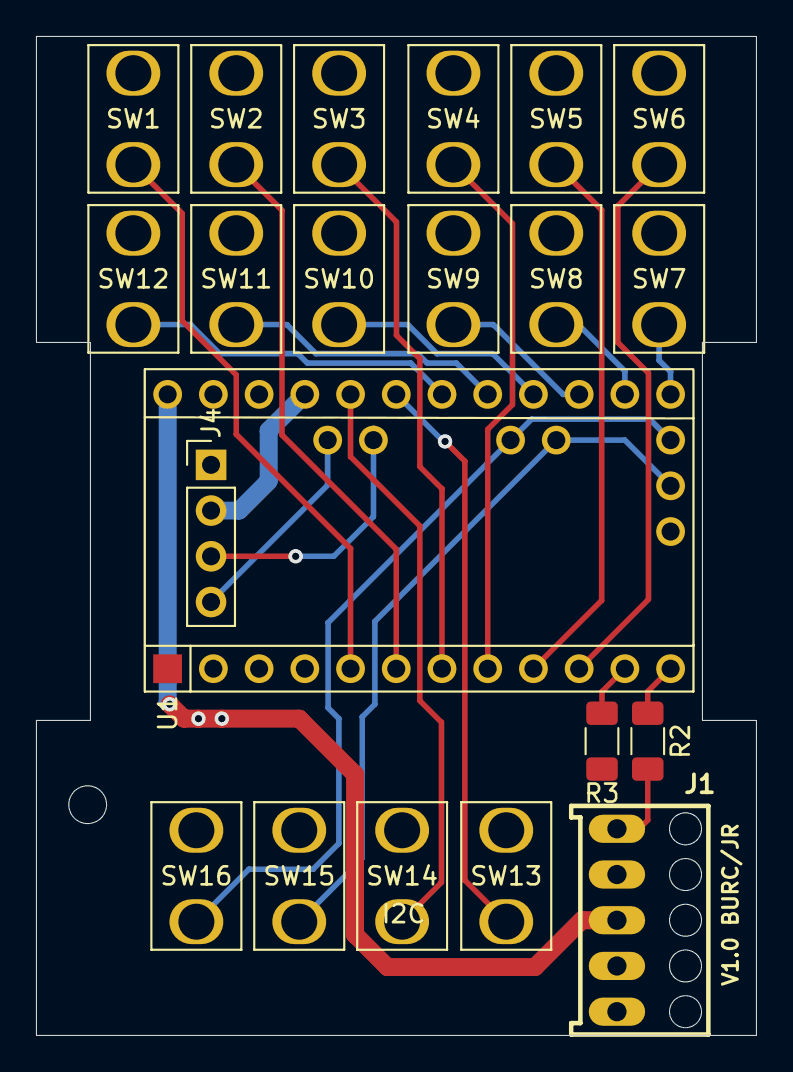
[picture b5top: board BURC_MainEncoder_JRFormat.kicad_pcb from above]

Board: 2 copper layers, 40.0 x 55.5 mm, 21 parts (0 on the bottom side), 24 nets.

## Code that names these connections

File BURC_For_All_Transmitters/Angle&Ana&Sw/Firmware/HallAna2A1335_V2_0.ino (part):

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 ========
  Phys Avr  Arduino
  Pin1 PB5  5   A0 RESET
  Pin2 PB3  3   A3 PWM
  Pin3 PB4  4   A2 PWM
  Pin4 GND  GND
  Pin5 PB0  0      PWM SDA
  Pin6 PB1  1      PWM
  Pin7 PB2  2   A1     SCL
  Pin8 VCC  VCC
                       P3022-V1-CW360
                       ANA HALL SENSOR
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                  |                     |    |                 |                            \
                  |                     |    |                 |                            |
                  |                     #    |                 |                            |
                  |                 POT #<--->2 PB3       PB2 7>--------------------o SCL   |
          100nF =====                   #    |       AVR       |                            |
                =====  OUT O-----.      |    |     ATtiny85    |                           /
                  |              |      |    |                 |                          | COMPATIBLE A1335
                  |              '----------->3 PB4       PB1 6>---.                       > I2C INTERFACE
                  |                     |    |                 |   |                      |
                  |                     |    |                 |   V RED LED               \
                  |                     |    |                 |   |                        |
                  |              O------o----+4 GND       PB0 5X------ o------------o SDA   |
                  |          GND |           '-----------------'   |   |                    |
                  |              |                             680 #    D PUSH BUTTON       |
                  |              |                                 |   |     CAL/@          /
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
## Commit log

2023-09-07 Create BURC system repo JR and Other
2023-09-07 Add 3d vues
2023-09-07 Add dashbord
2023-09-07 change to folder
2023-09-07 Add schematics
2023-09-07 update readme file
2023-09-11 Swap CPPM_IN/CPPM_OUT
2023-09-17 Update schematic switch board
2023-10-01 Update
    Corrections diverses:
    - perçages bouton reset, potentiomètre linéaire.
    - ajout pullup i2c
2023-10-01 Update drill switch
2024-01-04 remove files
2024-01-04 Compression fichiers et ajout fichiers fab
2024-01-04 Update gerber
2024-01-04 Update BURC page
2024-01-04 remove gerber into zip files
2024-02-12 Update Multiswitch board
    Remove several pads for the pcf8575 option
2024-02-12 add RCUL picture
2024-07-23 add schematic
2024-07-23 update firmwares
2024-07-24 add fuses attiny85 infos
2024-07-27 Add 8-16 switchs gerber board files
2024-07-27 add 8_16-Simple_Encoder schematic
2024-08-19 add remove resistor detail
2025-04-13 update firmware code
